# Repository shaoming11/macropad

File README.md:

# Shaoming's Macropad
This is my first project that involved the use of KiCad and Fusion 360. 

# Features
- 4 keyboard buttons
- RP2040 microcontroller
- Firmware connected to QMK
- 3D Printable Case using Fusion 360
- PCB designed using KiCad

# PCB

Schematic Layout

PCB Layout

Dimensions: 53.531 x 62.930 mm

# CAD Model

Model

Sketches

# Bill of Materials

Seeed XIAO RP2040 - since you're soldering, you can mount it SMD style! Please note it is significantly harder than doing it through-hole, so if it's your first time soldering I would avoid it.

MX-Style switches (4x)

0.91 inch OLED displays (1x)

Blank DSA keycaps (White)

M3x16mm screws (4x)

M3x5mx4mm heatset inserts (4x)

# What I learned
I learned about the basics of PCB design through KiCad, exclusively working on schematics and PCB layout. Performing DRC helped me understand how to turn schematics into a printable PCB layout.

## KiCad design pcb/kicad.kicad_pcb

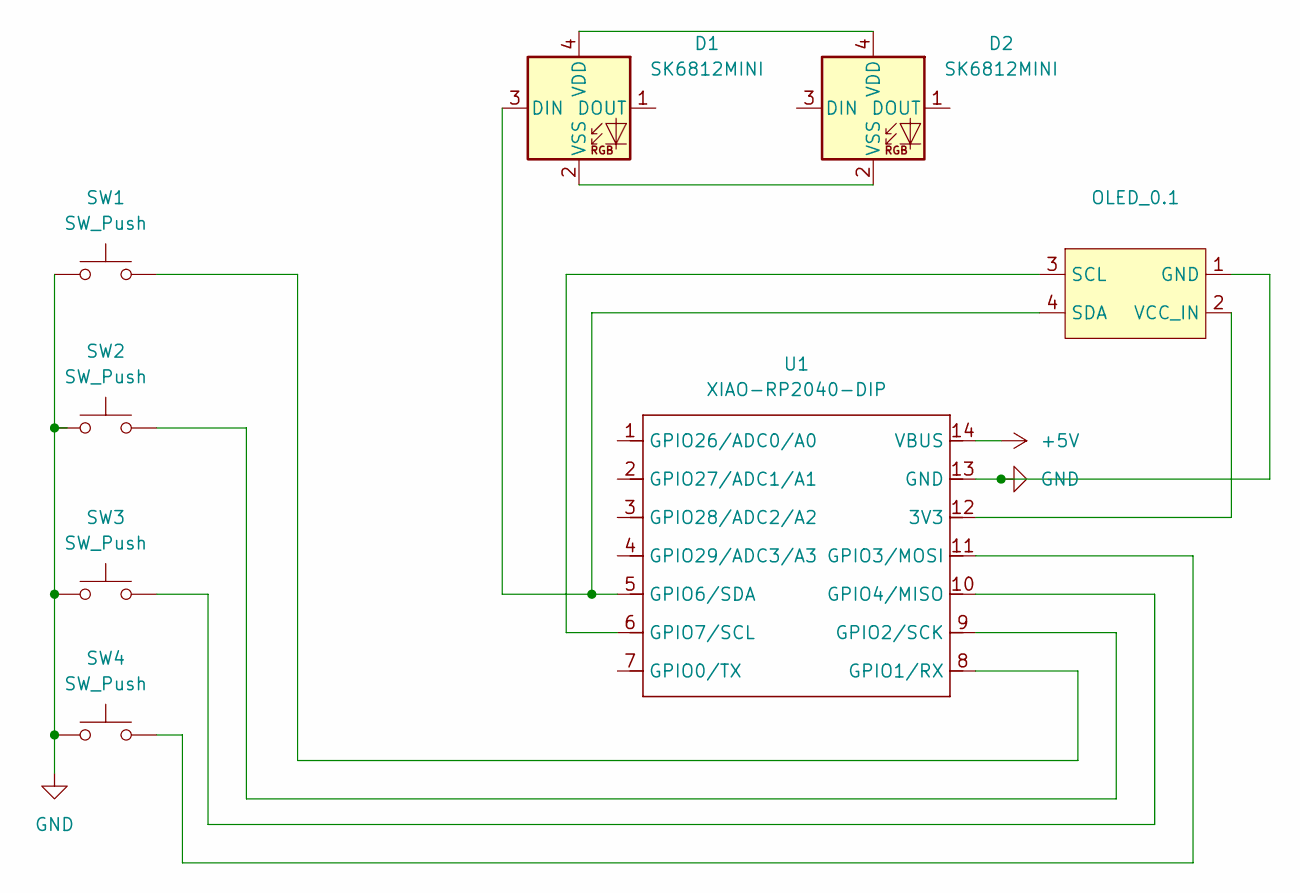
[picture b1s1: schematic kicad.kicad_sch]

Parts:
D1, D2: SK6812MINI; LED_SK6812MINI_PLCC4_3.5x3.5mm_P1.75mm
OLED_0.1: SSD1306-0.91-OLED-4pin-128x32
SW1, SW2, SW3, SW4: SW_Push; SW_Cherry_MX_1.00u_PCB
U1: XIAO-RP2040-DIP

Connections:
+5V: U1.14 (VBUS)
GND: OLED_0.1.1 (GND), SW1.1, SW2.1, SW3.1, SW4.1, U1.13 (GND)
unnamed: D1.3 (DIN), OLED_0.1.4 (SDA), U1.5 (GPIO6/SDA)
unnamed: D1.4 (VDD), D2.4 (VDD)
unnamed: D1.2 (VSS), D2.2 (VSS)
unnamed: OLED_0.1.3 (SCL), U1.6 (GPIO7/SCL)
unnamed: OLED_0.1.2 (VCC_IN), U1.12 (3V3)
unnamed: SW1.2, U1.8 (GPIO1/RX)
unnamed: SW2.2, U1.9 (GPIO2/SCK)
unnamed: SW4.2, U1.11 (GPIO3/MOSI)
unnamed: SW3.2, U1.10 (GPIO4/MISO)

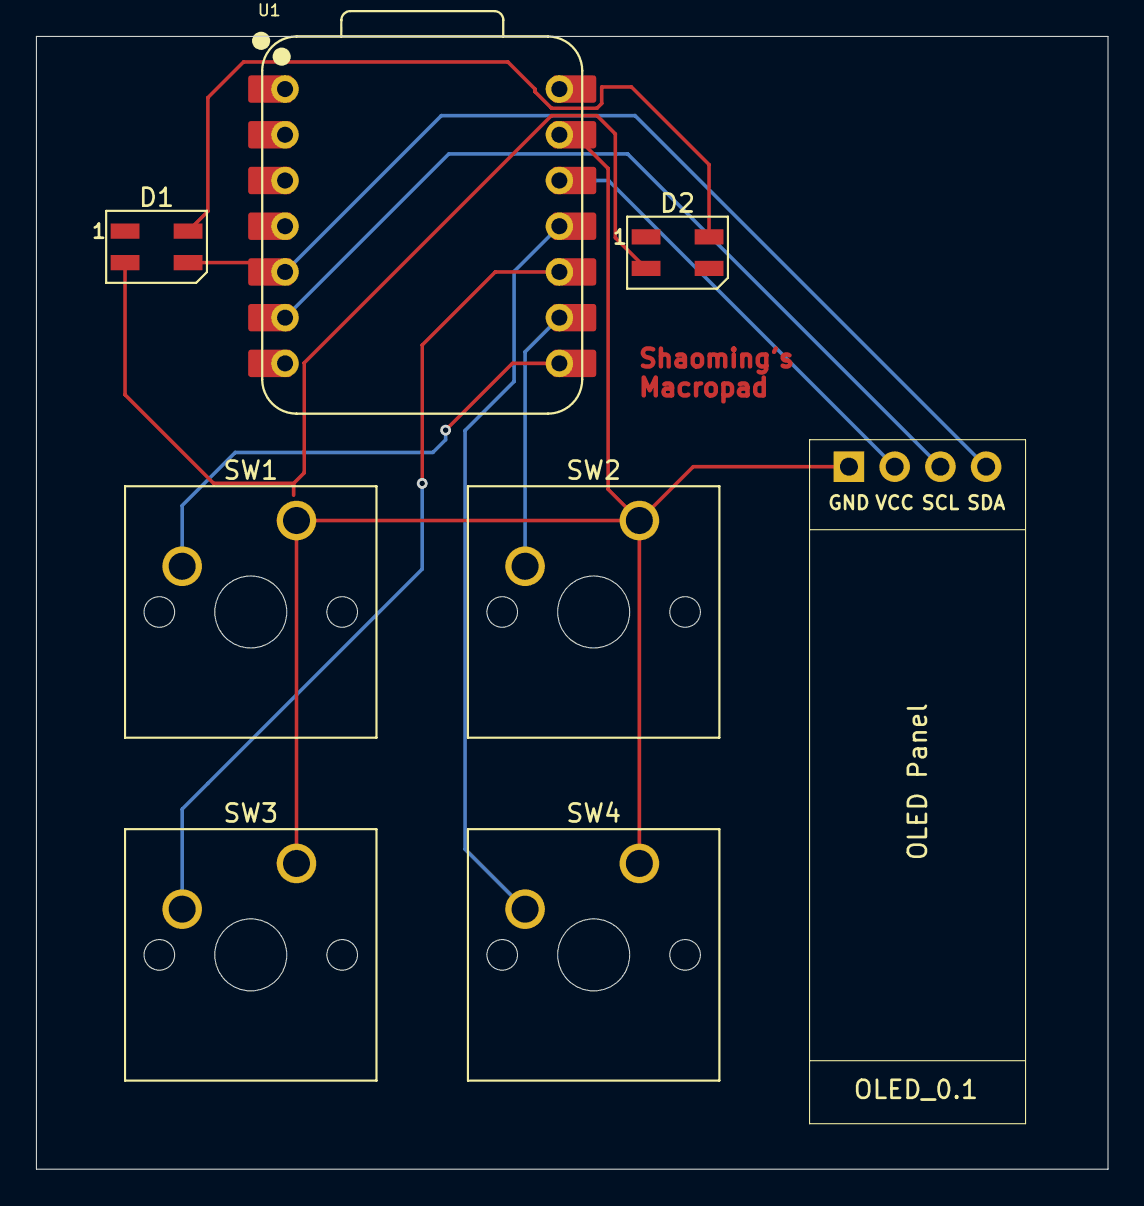
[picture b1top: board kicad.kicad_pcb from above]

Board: 2 copper layers, 59.5 x 62.9 mm, 8 parts (0 on the bottom side), 10 nets.

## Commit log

2025-12-25 feat: insert cad models, pcb layout, import OPL KiCad Library & docs: README.md
2025-12-25 docs: Update README with PCB and CAD Model information
    Added sections for PCB, CAD Model, and Bill of Materials with relevant images and details.
2025-12-25 docs: improve README formatting for reader visbility
2025-12-27 update cad and pcb to include lcd display
2025-12-28 firmware with QMK
2025-12-28 Fix typos and update PCB dimensions in README
    Corrected typos and updated dimensions in the README.
